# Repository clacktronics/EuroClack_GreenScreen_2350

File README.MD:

# EuroClack Green Screen 2350

EuroClack Green Screen 2350 is a **programmable Eurorack synthesizer module built around the Raspberry Pi RP2350B**. It combines stereo audio input/output, control-voltage (CV) and gate interfaces, a colour display, hands-on controls, microSD storage and USB connectivity.

The module provides a general-purpose platform for developing digital instruments, audio effects, sequencers and modulation tools within a Eurorack system. Application firmware defines its musical behaviour, while the audio, CV and gate interfaces connect it to the rest of the patch. The display and physical controls support interactive visual instruments and direct parameter editing.

The included firmware demonstrates a Tempest-inspired game and a double-pendulum simulation with sound. Effects processing, sampling and sequencing require their own application firmware.

## Main functions

| Function | Circuit | Purpose |
|---|---|---|
| Processing | U1, RP2350B in an 80-pin package | Runs the application, processes audio and CV, generates gates and manages the interface. |
| Program storage | U4, W25Q128JVS | External 128-Mbit / 16-MiB flash for firmware and stored data. |
| Additional memory provision | U15, labelled `SRAM` | Shares the QSPI data/clock bus with a separate chip select. The actual memory part and capacity are unspecified. |
| Two audio inputs | U6 TL072 stages and U5 PCM1808 | Condition analog signals and convert them to digital audio for the processor over I²S. |
| Two audio outputs | U2 PCM5102 and output filters | Convert the processor's I²S stream into left/right analog audio. |
| Four CV inputs | U13/U20 amplifier stages and MCU ADC inputs | Scale and offset external control voltages for measurement by the processor. |
| Four gate-sensing paths | U19/U21 LM393 comparators | Detect gate/trigger levels: two share CV inputs and two use dedicated gate jacks. |
| Four CV outputs | U3 MCP4728 and U8/U17 amplifier stages | Convert four digitally programmed values into analog control voltages. |
| Two gate outputs | U18/U22 SN74LVC1T45 | Translate processor logic into nominal 0/5-V gate signals through series output resistors. |
| Display and controls | SPI display connections, two push encoders and buttons | Provide graphical feedback, parameter editing and navigation. |
| Storage and expansion | microSD, external I²C, USB-C device and USB-A host connections | Provide hardware paths for files, peripherals and computer/device communication, subject to firmware support. |

There are **six physical CV/gate input jacks**: two CV-only, two shared CV/gate and two gate-only. The shared inputs are measured by both an ADC path and a comparator path, allowing firmware to read a control voltage and detect gate transitions from the same connection.

## How signals move through the circuit

```text
Audio inputs --> analog conditioning --> PCM1808 ADC --I²S--> RP2350B
Audio outputs <-- output filters <----- PCM5102 DAC <--I²S-- RP2350B

CV inputs ----> scaling and offset -----------------------> MCU ADCs
Gate inputs --> comparator thresholds -------------------> MCU GPIO
CV outputs <--- amplifier stages <----- MCP4728 DAC <------ MCU control
Gate outputs <- 3.3-V to 5-V translation <----------------- MCU GPIO

                     RP2350B
                        |
         Display / encoders / buttons / microSD / USB / I²C
```

The audio converters handle continuous sampled sound. The separate CV DAC and gate circuitry let firmware interact with other modular instruments: reading modulation, following clock or trigger events, and generating control signals. The analog stages adapt these signals to the processor and converters; their resistor ratios and reference voltages determine the actual voltage ranges.

## Display, controls and example firmware

The supplied sketches target an **NV3030B colour TFT at 280 × 240 pixels in landscape orientation**. The schematic provides parallel eight-pin header and FFC display connections; the fitted panel must match the driver and pinout.

- [Tempest demo](demo_scripts/nv3030b_tempest/nv3030b_tempest.ino): an encoder-controlled arcade-style game with audio output.
- [Double-pendulum demo](demo_scripts/nv3030b_pendulum/nv3030b_pendulum.ino): a visual physics simulation whose second pendulum's X/Y position drives the left/right audio channels.

The sketches demonstrate display rendering, encoder input and audio generation. USB MIDI, sample playback, sequencing and effects require additional application firmware. See [PERIPHERALS.md](PERIPHERALS.md) for GPIO assignments, converter configuration and firmware considerations.

## Power and physical construction

Power enters through the ten-pin Eurorack connector J18 using +12 V, ground and −12 V. The design includes MOSFET protection circuitry, switching and linear regulators for its intended 5-V and 3.3-V rails, and a 3.3-V reference with an inverted reference for CV conditioning. The analog amplifier stages use the bipolar rails. USB-C VBUS is unconnected, so this design is intended to be self-powered rather than powered from a computer's USB port.

The PCB contains processor, jack/control and SD-extension sections. A 40-way FFC links the processor and jack sections, carrying signals and power; separate connections serve the SD extension. Cable orientation and pin mapping are documented in [PERIPHERALS.md](PERIPHERALS.md).

## Current development status

This is a prototype design with documented electrical issues. The existing [DESIGN_REVIEW.md](DESIGN_REVIEW.md) reports power-supply faults, input-protection gaps, audio coupling/mute issues and incorrect CV output scaling. In particular, **the intended ±5-V CV range is not an established working capability**: the review calculates approximately 0–1.65 V for the current CV output stage. Read that review before assembly or power-up.

This README documents the module's architecture and application scope. Electrical findings and validation limits are recorded in the design review.

## Project files

- `EuroClack - Green_Screen_2350.kicad_pro` — open this project in KiCad.
- `EuroClack - Green_Screen_2350.kicad_sch` — current circuit schematic.
- `EuroClack - Green_Screen_2350.kicad_pcb` — PCB layout.
- [libraries/README.md](libraries/README.md) — bundled custom libraries and dependencies. The schematic uses KiCad 10 format; the PCB uses KiCad 9 format.
- [PERIPHERALS.md](PERIPHERALS.md) — detailed connections and firmware reference.
- [DESIGN_REVIEW.md](DESIGN_REVIEW.md) — existing engineering review and limitations.
- `demo_scripts/` — example display, controls and audio sketches.

The root PDF represents an older RP2040 design; use the native RP2350 KiCad schematic as the source for this revision.

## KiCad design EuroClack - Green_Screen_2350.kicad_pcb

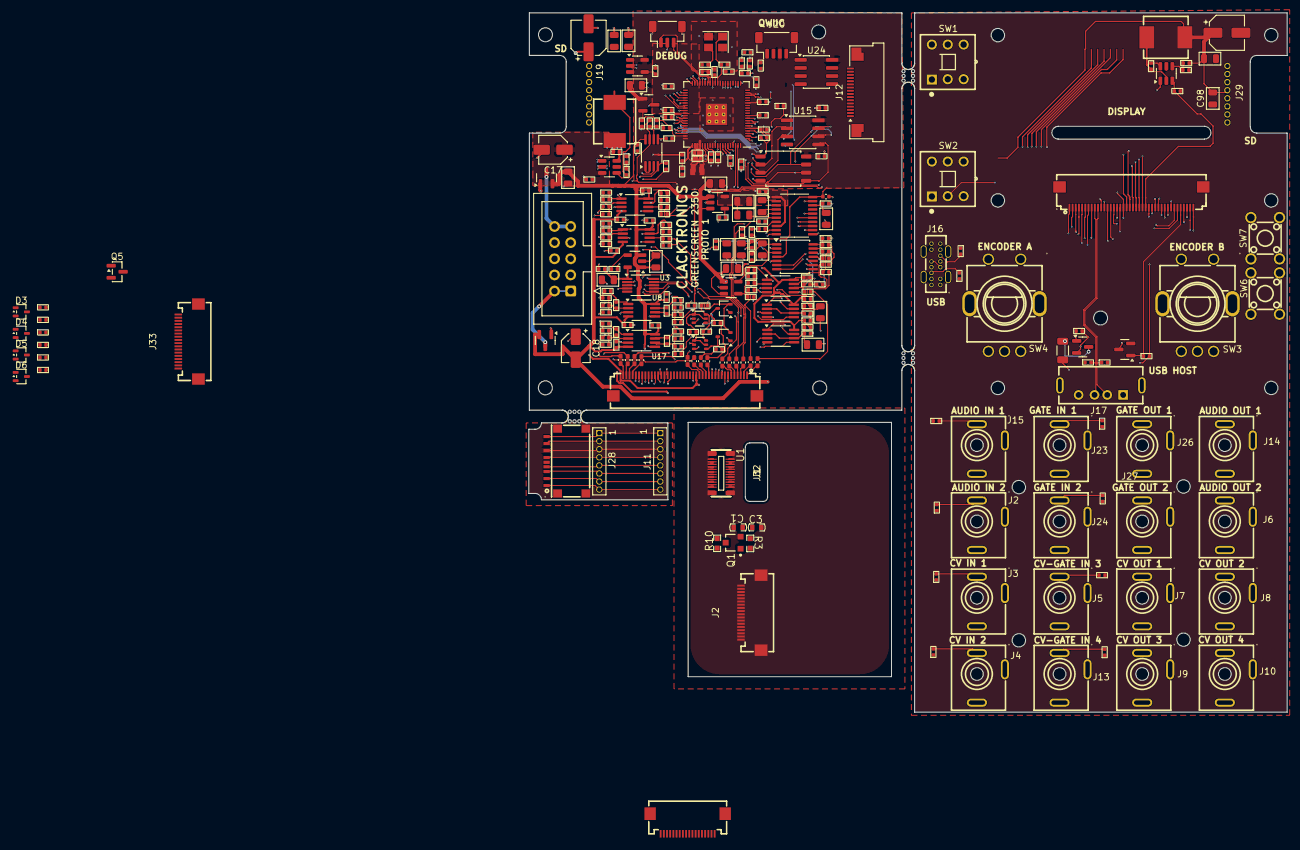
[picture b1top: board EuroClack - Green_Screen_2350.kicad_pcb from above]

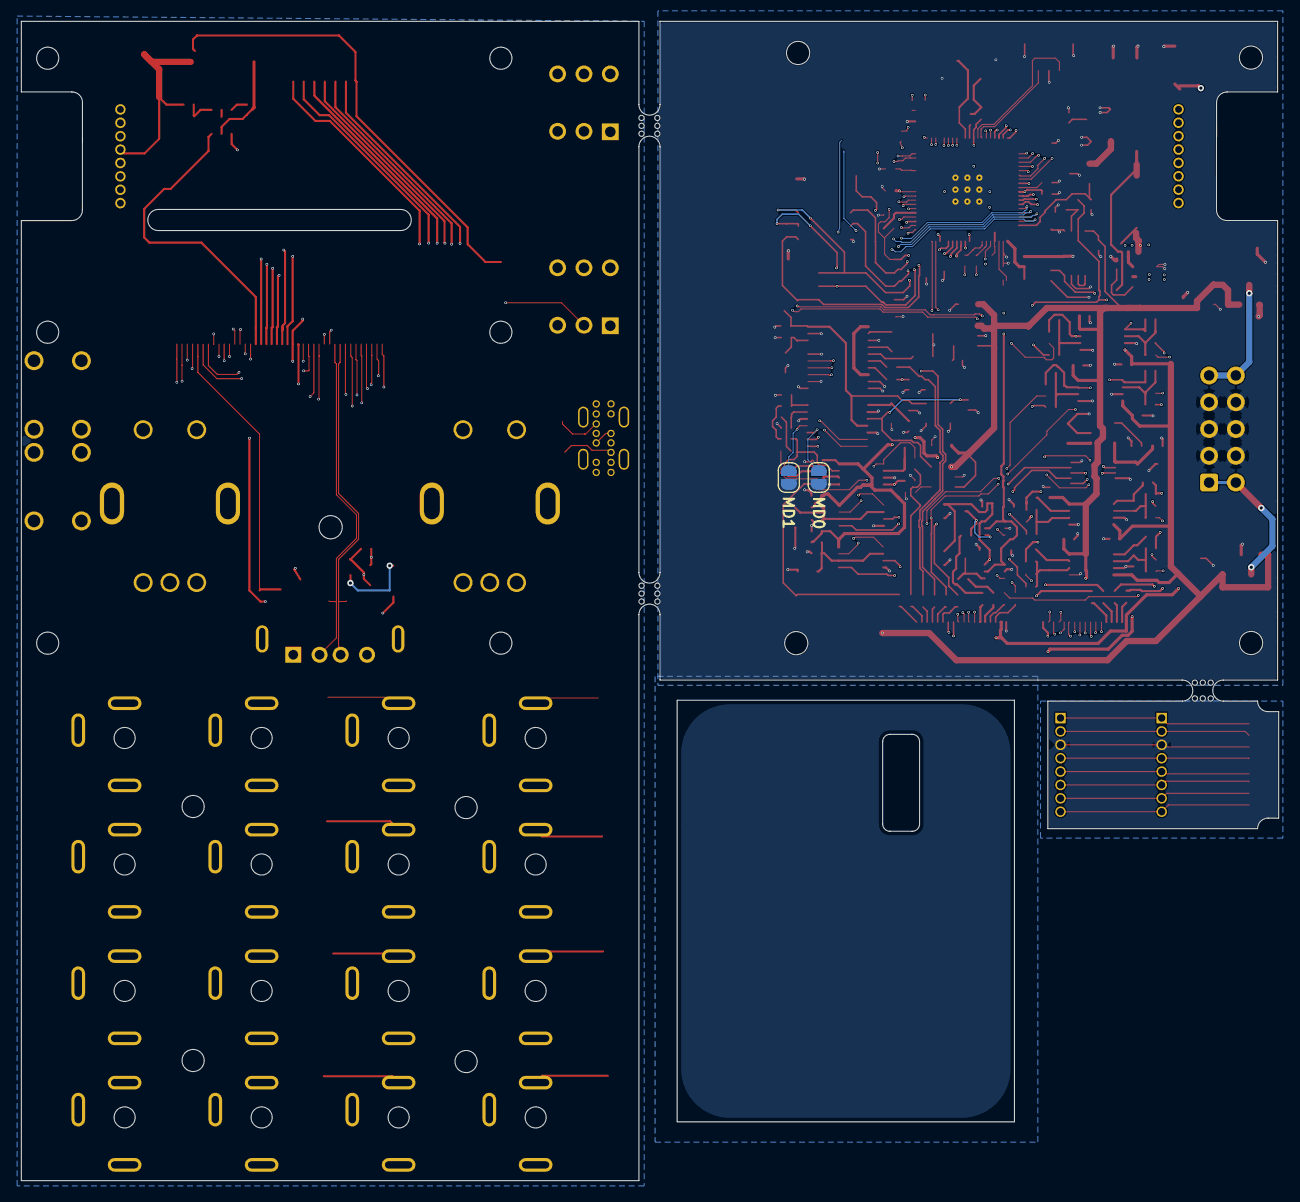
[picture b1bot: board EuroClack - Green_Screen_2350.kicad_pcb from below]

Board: 4 copper layers, 119.3 x 110.0 mm, 277 parts (2 on the bottom side), 228 nets.

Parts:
C1, C2, C7, C8: 2n2; C_0402_1005Metric
C1#2: Comment; C0603-1
C3, C6: 2u2; C_0805_2012Metric
C3#2: Comment; C0603-2
C4, C11, C13, C15, C21, C23, C24, C34, C45, C53, C57, C58, C60, C89, C95, C96, C98: 10uF; C_0805_2012Metric
C5, C12, C14, C16, C22, C25, C26, C37, C39, C40, C41, C42, C43, C44, C46, C47, C48, C49, C50, C51, C52, C54, C55, C56, C59, C61, C62, C63, C64, C70, C73, C74, C75, C76, C77, C78, C79, C80, C81, C82, C83, C84, C85, C86, C92, C93, C94, C97: 100n; C_0402_1005Metric
C9, C10: 1u; C_0402_1005Metric
C17, C18: 22uF; CP_Elec_4x5.4
C27, C28, C29, C30, C31, C32, C33, C67, C90, C91: 10p; C_0402_1005Metric
C38, C87: 220uF; CP_Elec_5x5.4
C65, C66: 15p; C_0402_1005Metric
C68, C69, C71, C72: 4.7u; C_0402_1005Metric
D1, D2, D3, D4, D5, D6: BAT54SW; SOT-323_SC-70
F1: nSMD005 150mA; R_1206_3216Metric
FB1, FB2, FB3, FB4, FB5, FB6, FB7, FB8, FB9, FB10, FB11, FB12, FB13, FB14: F; L_0402_1005Metric_Pad0.77x0.64mm_HandSolder
J1, J32: NV3030B QSPI; CONN-SMD_AXT524124
J1#2: C2982548; TF-SMD_TF-123-ARP9H15
J2, J3, J4, J5, J6, J7, J8, J9, J10, J13, J14, J15, J23, J24, J26, J27: Stereo Jack; AUDIO-TH_PJ-301C
J2#2, J3#2, J33: Conn_01x18; FPC-SMD_18P-P0.50_FPC-0.5-18P-HYH2.0
J11, J28: C22438074; CONN-TH_8P-P1.27_DEALON_DW127R-11-08-34
J12: Conn_01x16; Amphenol_F32Q-1A7x1-11016_1x16-1MP_P0.5mm_Horizontal
J16: C168704; USB-C-TH_TYPE-C-USB-14P
J17: USB_HOST; USB-A-TH_C42536
J18: Eurorack 10 pin socket; IDC-Header_2x05_P2.54mm_Vertical
J19, J29: C22438194; HDR-TH_8P-P1.27-H-M_1271WR-8P
J20: STEMMA_QT; JST_SH_BM04B-SRSS-TB_1x04-1MP_P1.00mm_Vertical
J21, J22: C2856837; FPC-SMD_40P-P0.50_XUNPU_FPC-05FB-40PH20
J25: SM03B-SRSS-TB; JST_SH_BM03B-SRSS-TB_1x03-1MP_P1.00mm_Vertical
JP1, JP2: SolderJumper_2_Open; SolderJumper-2_P1.3mm_Open_RoundedPad1.0x1.5mm
L2, L4: 10uH 4A; FXL0630-100-M
L3: 3.3u; L_pol_2016
Q1, Q4, Q5: AO3400A; SOT-23
Q1#2: Comment; SOT23A
Q2, Q3: AO3401A; SOT-23
R1, R2, R5, R15, R16, R23, R44, R53, R58, R59, R60, R61: 1k; R_0402_1005Metric
R3, R10#2: Comment; R0603
R3#2, R14, R18, R22, R25, R35, R38, R41, R50, R52, R92, R99, R100, R103, R104, R105, R106: 10k; R_0402_1005Metric
R6: 33; R_0402_1005Metric
R9, R29, R32, R46: 68k; R_0402_1005Metric
R10, R12, R27, R30, R33, R47: 33k; R_0402_1005Metric
R11, R28, R31, R34, R45, R48, R49, R51, R97, R108: 100k; R_0402_1005Metric
R13, R26, R37, R40: 6.49k; R_0402_1005Metric
R17, R36, R39, R42: 1.96k; R_0402_1005Metric
R24, R43: 27; R_0402_1005Metric
R54, R55, R56, R57: 220R; R_0402_1005Metric
R85, R86, R87, R88, R89, R90, R95, R96: 1M; R_0402_1005Metric
R91: 75k; R_0402_1005Metric
R93, R94: 5.1k; R_0402_1005Metric
R98: 22k; R_0402_1005Metric
R101, R102: R_0402_1005Metric
R107: 10R; R_0402_1005Metric
SW1, SW2: SW-TH_PS-8556DVA-6PN
SW3, SW4: RotaryEncoder_Switch; SW-TH_EC11XXXXXXXX
SW6, SW7: SW_Push; SW-TH_4P-L5.0-W5.0-P4.50-LS6.5
U1: Comment; TK014F1246-24P
U1#2: RP2350_80QFN; RP2350-QFN-80-1EP_10x10_P0.4mm_EP3.4x3.4mm_ThermalVias
U2: PCM5102; TSSOP-20_4.4x6.5mm_P0.65mm
U3: MCP4728; MSOP-10_3x3mm_P0.5mm
U4: W25Q128JVS; SOIC-8_5.3x5.3mm_P1.27mm
U5: PCM1808PWR; TSSOP-14_4.4x5mm_P0.65mm
U6, U8, U11, U13, U17, U20: TL072; MSOP-8_3x3mm_P0.65mm
U7: REF3033; SOT-23
U9, U14, U16: SPX3819M5-L-3-3; SOT-23-5
U10: SPX3819M5-L-5-0; SOT-23-5
U12, U23: TPS54302; SOT-23-6
U15: SRAM; SOIC-8_3.9x4.9mm_P1.27mm
U18, U22: SN74LVC1T45DCK; SOT-363_SC-70-6
U19, U21: LM393; MSOP-8_3x3mm_P0.65mm
U24: FM24CL16B; SOIC-8_3.9x4.9mm_P1.27mm
Y1: ABM8-272-T3; Crystal_SMD_3225-4Pin_3.2x2.5mm
mouse-bite-2mm-slot, mouse-bite-2mm-slot#2, mouse-bite-2mm-slot#3: VAL**; mouse-bite-2mm-slot

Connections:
3.3V: C1#2.1, C3#2.1, R3.1, U1.15, U1.17, U1.23
$1N2: Q1#2.3, R10#2.1
+1V1: C69.1, C70.1, C72.1, C73.1, L3.1, U1#2.10 (DVDD), U1#2.32 (DVDD), U1#2.51 (DVDD), U1#2.65 (VREG_FB)
+3.3V: C15.1, C16.1, C55.1, C63.1, C64.1, C68.1, C74.1, C75.1, C76.1, C77.1, C78.1, C79.1, C80.1, C81.2, C82.1, C83.1, C93.2, J1.15, J1.17, J1.23, J2#2.3, J2#2.4, J2#2.17, J3#2.1, J20.3, J32.15, J32.17, J32.23, J33.3, J33.4, J33.17, R3#2.1, R6.1, R22.1, R103.2, R104.2, R105.2, R106.2, U1#2.5 (IOVDD), U1#2.15 (IOVDD), U1#2.24 (IOVDD), U1#2.29 (IOVDD), U1#2.41 (IOVDD), U1#2.50 (IOVDD), U1#2.60 (IOVDD), U1#2.64 (VREG_VIN), U1#2.68 (USB_OTP_VDD), U1#2.69 (QSPI_IOVDD), U1#2.76 (IOVDD), U2.17 (XSMT), U2.20 (DVDD), U4.8 (VCC), U5.4 (VDD), U14.5 (OUT), U15.8 (VCC), U18.1 (VCCA), U18.5 (DIR), U22.1 (VCCA), U22.5 (DIR), U24.8 (VDD)
+3.3VA: C21.1, C22.1, U3.1 (VDD), U9.5 (OUT)
+5V: C38.1, C57.1, C58.1, C60.1, C92.1, C94.1, D1.2 (K), D2.2 (K), D3.2 (K), D4.2 (K), D5.2 (K), D6.2 (K), J21.17, L2.2, R91.2, U7.1 (IN), U14.1 (IN), U14.3 (EN), U18.6 (VCCB), U22.6 (VCCB)
+5VA: C13.1, C14.1, U5.3 (VCC), U10.5 (OUT)
+12V: C17.1, C23.1, C24.1, C39.1, C41.1, C43.1, C46.1, C47.1, C49.1, C51.1, C59.2, C62.1, C85.2, C95.2, C96.1, J21.25, Q2.2 (S), R49.2, R51.2, U6.8 (V+), U8.8 (V+), U9.1 (IN), U9.3 (EN), U10.1 (IN), U10.3 (EN), U11.8 (V+), U12.3 (VIN), U13.8 (V+), U16.1 (IN), U16.3 (EN), U17.8 (V+), U19.8 (V+), U20.8 (V+), U21.8 (V+), U23.3 (VIN)
-12V: C18.2, C40.1, C42.1, C44.1, C48.1, C50.1, C52.1, Q1.2 (S), U6.4 (V-), U8.4 (V-), U11.4 (V-), U13.4 (V-), U17.4 (V-), U20.4 (V-)
/3V3_DAC: C53.1, C54.1, U2.1 (CPVDD), U2.8 (AVDD), U16.5 (OUT)
/3V3_SD_SCREEN: C87.1, C89.1, C98.1, J12.8, J12.9, J12.16, J29.5, L4.2, R97.2
/5V_JACK: J22.17, Q3.2 (S), R99.2, R100.2
/AUDIO_IN_1_JACK: J15.T, J22.1, R86.2
/AUDIO_IN_1_MICRO: FB1.1, J21.1
/AUDIO_IN_2_JACK: J2.T, J22.2, R85.2
/AUDIO_IN_2_MICRO: FB2.1, J21.2
/AUDIO_L_IN: C10.1, C27.2, R12.2, U6.7
/AUDIO_OUT_1_JACK: J14.T, J22.3
/AUDIO_OUT_1_MICRO: FB6.2, J21.3
/AUDIO_OUT_2_JACK: J6.T, J22.4
/AUDIO_OUT_2_MICRO: FB7.2, J21.4
/AUDIO_R_IN: C9.1, C28.2, R27.2, U6.1
/CV_GATE_IN_3_JACK: J5.T, J22.5, R89.2
/CV_GATE_IN_3_MICRO: FB12.1, J21.5
/CV_GATE_IN_4_JACK: J13.T, J22.6, R90.2
/CV_GATE_IN_4_MICRO: FB5.1, J21.6
/CV_IN_1: FB3.2, R31.1
/CV_IN_1_JACK: J3.T, J22.15, R87.2
/CV_IN_1_MICRO: FB3.1, J21.15
/CV_IN_2_JACK: J4.T, J22.16, R88.2
/CV_IN_2_MICRO: FB4.1, J21.16
/CV_OUT_1: FB8.1, R18.2, R57.2
/CV_OUT_1_JACK: J7.T, J22.40
/CV_OUT_1_MICRO: FB8.2, J21.40
/CV_OUT_2: FB9.1, R35.2, R56.2
/CV_OUT_2_JACK: J8.T, J22.37
/CV_OUT_2_MICRO: FB9.2, J21.37
/CV_OUT_3: FB10.1, R38.2, R55.2
/CV_OUT_3_JACK: J9.T, J22.39
/CV_OUT_3_MICRO: FB10.2, J21.39
/CV_OUT_4: FB11.1, R41.2, R54.2
/CV_OUT_4_JACK: J10.T, J22.38
/CV_OUT_4_MICRO: FB11.2, J21.38
/ENC1_A_JACK: J22.31, SW3.A
/ENC1_A_MICRO: J21.31, U1#2.37 (GPIO29)
/ENC1_B_JACK: J22.32, SW3.B
/ENC1_B_MICRO: J21.32, U1#2.38 (GPIO30)
/ENC1_SW_JACK: J22.30, SW3.S1
/ENC1_SW_MICRO: J21.30, U1#2.36 (GPIO28)
/ENC2_A_JACK: J22.34, SW4.A
/ENC2_A_MICRO: J21.34, U1#2.40 (GPIO32)
/ENC2_B_JACK: J22.35, SW4.B
/ENC2_B_MICRO: J21.35, U1#2.42 (GPIO33)
/ENC2_SW_JACK: J22.33, SW4.S1
/ENC2_SW_MICRO: J21.33, U1#2.39 (GPIO31)
/GATE_IN_1_JACK: J22.7, J23.T, R95.2
/GATE_IN_1_MICRO: J21.7, R61.1
/GATE_IN_2_JACK: J22.8, J24.T, R96.2
/GATE_IN_2_MICRO: J21.8, R60.1
/GATE_OUT_1_JACK: J22.13, J26.T
/GATE_OUT_1_MICRO: FB14.2, J21.13
/GATE_OUT_2_JACK: J22.14, J27.T
/GATE_OUT_2_MICRO: FB13.2, J21.14
/GND_JACK: C98.2, J2.S, J3.S, J4.S, J5.S, J6.S, J7.S, J8.S, J9.S, J10.S, J13.S, J14.S, J15.S, J16.A1 (GND), J16.A12 (GND), J16.B1 (GND), J16.B12 (GND), J16.S1 (SHIELD), J17.4 (GND), J17.5 (Shield), J22.18, J23.S, J24.S, J26.S, J27.S, J29.3, Q4.2 (S), R85.1, R86.1, R87.1, R88.1, R89.1, R90.1, R93.1, R94.1, R95.1, R96.1, R101.1, R102.2, SW1.1, SW2.1, SW3.C, SW3.S2, SW4.C, SW4.S2, SW6.1, SW7.1
/HSTX12_DC: J12.1, U1#2.11 (GPIO12)
/HSTX13_CS: J12.2, U1#2.12 (GPIO13)
/HSTX14_SCK: J12.3, U1#2.13 (GPIO14)
/HSTX15_DIN: J12.4, U1#2.14 (GPIO15)
/HSTX16_RST: J12.5, U1#2.16 (GPIO16)
/HSTX17_BLK: R107.2, R108.1, U1#2.17 (GPIO17)
/I2C_DAC_SCL: J21.21, R105.1, U1#2.22 (GPIO22), U3.2 (SCL)
/I2C_DAC_SDA: J21.22, R106.1, U1#2.23 (GPIO23), U3.3 (SDA)
/I2S_ADC_BCK: U1#2.7 (GPIO9), U5.8 (BCK)
/I2S_ADC_DOUT: U1#2.9 (GPIO11), U5.9 (DOUT)
/I2S_ADC_LRCK: U1#2.8 (GPIO10), U5.7 (LRCK)
/I2S_ADC_MD0: JP2.2 (B), U5.10 (MD0)
/I2S_ADC_MD1: JP1.2 (B), U5.11 (MD1)
/I2S_ADC_SCKI: U1#2.21 (GPIO21), U5.6 (SCKI)
/I2S_DAC_BCK: U1#2.3 (GPIO6), U2.13 (BCK)
/I2S_DAC_DIN: U1#2.6 (GPIO8), U2.14 (DIN)
/I2S_DAC_LRCK: U1#2.4 (GPIO7), U2.15 (LRCK)
/LCD_CS: J1.1, J2#2.8, J3#2.7, J32.1, J33.8
/LCD_DC: J2#2.7, J3#2.8, J33.7
/LCD_RST: J1.9, J2#2.11, J32.9, J33.11
/LCD_TE: J1.14, J3#2.11, J32.14
/LEDK: J1.16, J2#2.2, J32.16, J33.2
/LED_K: J12.6, Q5.3 (D)
/MCU_CV_IN_1: C29.2, R30.2, U1#2.49 (GPIO40_ADC0), U13.1
/MCU_CV_IN_2: C30.2, R33.2, U1#2.52 (GPIO41_ADC1), U13.7
/MCU_CV_IN_3: C32.2, R10.2, U1#2.53 (GPIO42_ADC2), U20.1
/MCU_CV_IN_4: C33.2, R47.2, U1#2.54 (GPIO43_ADC3), U20.7
/MCU_GATE_IN_1: U1#2.55 (GPIO44_ADC4), U21.1
/MCU_GATE_IN_2: U1#2.56 (GPIO45_ADC5), U21.7
/MCU_GATE_IN_3: U1#2.57 (GPIO46_ADC6), U19.1
/MCU_GATE_IN_4: U1#2.58 (GPIO47_ADC7), U19.7
/MCU_GATE_OUT_1: U1#2.18 (GPIO18), U18.3 (A)
/MCU_GATE_OUT_2: U1#2.19 (GPIO19), U22.3 (A)
/QSPI_D1: J1.3, J3#2.4, J32.3
/QSPI_D2: J1.6, J3#2.5, J32.6
/QSPI_D3: J1.5, J3#2.6, J32.5
/QSPI_SCLK: U1#2.71 (QSPI_SCLK), U4.6 (CLK), U15.6 (CLK)
/QSPI_SD0: U1#2.72 (QSPI_SD0), U4.5 (DI(IO0)), U15.5 (DI(IO0))
/QSPI_SD1: U1#2.74 (QSPI_SD1), U4.2 (DO(IO1)), U15.2 (DO(IO1))
/QSPI_SD2: U1#2.73 (QSPI_SD2), U4.3 (IO2), U15.3 (IO2)
/QSPI_SD3: U1#2.70 (QSPI_SD3), U4.7 (IO3), U15.7 (IO3)
/SD_CLK: J19.5, U1#2.43 (GPIO34)
/SD_CMD: J19.3, U1#2.44 (GPIO35)
/SD_DAT0: J19.7, U1#2.45 (GPIO36)
/SD_DAT1: J19.8, U1#2.46 (GPIO37)
/SD_DAT2: J19.1, U1#2.47 (GPIO38)
/SD_DAT3: J19.2, U1#2.48 (GPIO39)
/SD_GND: J1#2.6 (VSS), J11.3, J28.3
/SPI MOSI: J1.2, J2#2.10, J3#2.3, J32.2, J33.10
/SPI_SCK: J1.4, J2#2.9, J3#2.2, J32.4, J33.9
/STEMMA_SCL: J12.12, J20.1, J21.19, R103.1, U1#2.2 (GPIO5), U24.6 (SCL)
/STEMMA_SDA: J12.13, J20.2, J21.20, R104.1, U1#2.1 (GPIO4), U24.5 (SDA)
/SWCLK: J25.1, U1#2.33 (SWCLK)
/SWD: J25.3, U1#2.34 (SWD)
/SW_RUN_JACK: J22.27, SW7.2
/SW_USR1_JACK: J22.28, SW1.2
/SW_USR2_JACK: J22.29, SW2.2
/TP_INT: J1.22, J2#2.16, J3#2.14, J12.15, J32.22, J33.16
/TP_RST: J1.21, J2#2.15, J12.14, J32.21, J33.15
/TP_SCL: J1.19, J2#2.13, J3#2.12, J32.19, J33.13
/TP_SDA: J1.20, J2#2.14, J3#2.13, J32.20, J33.14
/USB_DM_JACK: J16.A7 (D-), J16.B7 (D-), J22.12
/USB_DN: J21.12, R43.1
/USB_DP: J21.11, R24.1
/USB_DP_JACK: J16.A6 (D+), J16.B6 (D+), J22.11
/USB_HOST_DM_JACK: J17.2 (D-), J22.10, R102.1
/USB_HOST_DM_MICRO: J21.10, U1#2.78 (GPIO1)
/USB_HOST_DP_JACK: J17.3 (D+), J22.9, R101.2
/USB_HOST_DP_MICRO: J21.9, U1#2.79 (GPIO2)
/VREF_ADC: C37.1, C84.1, R25.1, U1#2.59 (ADC_AVDD), U7.2 (OUT)
/VREF_ADC_NEG: R9.1, R13.1, R14.2, R26.1, R29.1, R32.1, R37.1, R40.1, R46.1, U11.7
/VREG_AVDD: C71.1, R6.2, U1#2.61 (VREG_AVDD)
/VREG_LX: L3.2, U1#2.63 (VREG_LX)
/XIN: C65.1, U1#2.30 (XIN), Y1.1
/XOUT: R5.1, U1#2.31 (XOUT)
/~PSRAM_CS: R22.2, U1#2.77 (GPIO0), U15.1 (~CS)
/~QSPI_SS: R3#2.2, R23.1, U1#2.75 (QSPI_SS), U4.1 (~CS)
/~SW_MENU_BOOT_JACK: J22.26, SW6.2
/~SW_MENU_BOOT_MICRO: J21.26, R23.2, U1#2.26 (GPIO25)
/~SW_RUN_MICRO: J21.27, U1#2.35 (RUN)
/~SW_USR1_MICRO: J21.28, U1#2.27 (GPIO26)
/~SW_USR2_MICRO: J21.29, U1#2.28 (GPIO27)
/~USBH_PWR_EN_JACK: J22.36, Q4.1 (G), R100.1
/~USBH_PWR_EN_MICRO: J21.36, U1#2.25 (GPIO24)
BL_CTR: Q1#2.1, R3.2
GND: C1.2, C1#2.2, C2.2, C3#2.2, C4.2, C5.2, C6.2, C7.2, C8.2, C11.2, C12.2, C13.2, C14.2, C15.2, C16.2, C17.2, C18.1, C21.2, C22.2, C23.2, C24.2, C25.2, C26.2, C34.2, C37.2, C38.2, C39.2, C40.2, C41.2, C42.2, C43.2, C44.2, C45.2, C46.2, C47.2, C48.2, C49.2, C50.2, C51.2, C52.2, C53.2, C54.2, C55.2, C57.2, C58.2, C59.1, C60.2, C61.2, C62.2, C63.2, C64.2, C65.2, C66.2, C68.2, C69.2, C70.2, C71.2, C72.2, C73.2, C74.2, C75.2, C76.2, C77.2, C78.2, C79.2, C80.2, C81.1, C82.2, C83.2, C84.2, C85.1, C87.2, C89.2, C92.2, C93.1, C94.2, C95.1, C96.2, C97.2, D1.1 (A), D2.1 (A), D3.1 (A), D4.1 (A), D5.1 (A), D6.1 (A), J1.13, J1.18, J1.24, J2#2.1, J2#2.5, J2#2.6, J2#2.12, J2#2.18, J3#2.15, J12.10, J12.11, J18.3, J18.4, J18.5, J18.6, J18.7, J18.8, J20.4, J21.18, J25.2, J25.MP (MountPin), J32.13, J32.18, J32.24, J33.1, J33.5, J33.6, J33.12, J33.18, JP1.1 (A), JP2.1 (A), Q1.1 (G), Q1#2.2, Q2.1 (G), Q5.2 (S), R50.1, R52.1, R92.1, R98.1, R108.2, U1.13, U1.18, U1.24, U1.25, U1#2.62 (VREG_PGND), U1#2.81 (GND), U2.3 (CPGND), U2.9 (AGND), U2.10 (DEMP), U2.11 (FLT), U2.12 (SCK), U2.16 (FMT), U2.19 (DGND), U3.4 (~LDAC), U3.10 (VSS), U4.4 (GND), U5.2 (AGND), U5.5 (DGND), U5.12 (FMT), U6.3 (+), U6.5 (+), U7.3 (GND), U8.3 (+), U8.5 (+), U9.2 (GND), U10.2 (GND), U11.3 (+), U11.5 (+), U12.1 (GND), U13.3 (+), U13.5 (+), U14.2 (GND), U15.4 (GND), U16.2 (GND), U17.3 (+), U17.5 (+), U18.2 (GND), U19.4 (V-), U20.3 (+), U20.5 (+), U21.4 (V-), U22.2 (GND), U23.1 (GND), U24.4 (VSS), Y1.2, Y1.4
LED-: R10#2.2, U1.16
unnamed: C1.1, FB6.1, R1.2
unnamed: C2.1, FB7.1, R2.2
unnamed: C9.2, R16.1
unnamed: C10.2, R15.1
unnamed: C31.2, R57.1, U8.1
unnamed: C66.1, R5.2, Y1.3
unnamed: C67.2, R56.1, U8.7
unnamed: C90.2, R55.1, U17.1
unnamed: C91.2, R54.1, U17.7
unnamed: D1.3 (COM), R53.1, U22.4 (B)
unnamed: D2.3 (COM), R44.1, U18.4 (B)
unnamed: D3.3 (COM), R60.2, U21.5 (+)
unnamed: D4.3 (COM), R61.2, U21.3 (+)
unnamed: D5.3 (COM), R59.2, U19.5 (+)
unnamed: D6.3 (COM), R58.2, U19.3 (+)
unnamed: FB1.2, R11.1
unnamed: FB2.2, R28.1
unnamed: FB4.2, R34.1
unnamed: FB5.2, R48.1, R59.1
unnamed: FB12.2, R45.1, R58.1
unnamed: FB13.1, R53.2
unnamed: FB14.1, R44.2
unnamed: J1#2.5 (CLK), J11.4, J28.4
unnamed: J1#2.3 (CMD), J11.6, J28.6
unnamed: J1#2.7 (DAT0), J11.2, J28.2
unnamed: J1#2.8 (DAT1), J11.1, J28.1
unnamed: J1#2.1 (DAT2), J11.8, J28.8
unnamed: J1#2.2 (DAT3/CD), J11.7, J28.7
unnamed: J1#2.4 (VDD), J11.5, J28.5
unnamed: J16.A5 (CC1), R93.2
unnamed: J16.B5 (CC2), R94.2
unnamed: F1.2, J17.1 (VBUS)
unnamed: J18.1, J18.2, Q1.3 (D)
unnamed: J18.9, J18.10, Q2.3 (D)
unnamed: F1.1, Q3.3 (D)
unnamed: Q3.1 (G), Q4.3 (D), R99.1
unnamed: Q5.1 (G), R107.1
unnamed: R43.2, U1#2.66 (USB_DM)
unnamed: R24.2, U1#2.67 (USB_DP)
unnamed: C3.2, U2.4 (CAPM)
unnamed: C3.1, U2.2 (CAPP)
unnamed: C4.1, C5.1, U2.18 (LDOO)
unnamed: R1.1, U2.6 (OUTL)
unnamed: R2.1, U2.7 (OUTR)
unnamed: C6.1, U2.5 (VNEG)
unnamed: R17.1, U3.6 (VOUTA)
unnamed: R36.1, U3.7 (VOUTB)
unnamed: R39.1, U3.8 (VOUTC)
unnamed: R42.1, U3.9 (VOUTD)
unnamed: C7.1, R16.2, U5.13 (VINL)
unnamed: C8.1, R15.2, U5.14 (VINR)
unnamed: C11.1, C12.1, U5.1 (VREF)
unnamed: C28.1, R27.1, R28.2, U6.2 (-)
unnamed: C27.1, R11.2, R12.1, U6.6 (-)
unnamed: C31.1, R13.2, R17.2, R18.1, U8.2 (-)
unnamed: C67.1, R26.2, R35.1, R36.2, U8.6 (-)
unnamed: C25.1, U9.4 (BP)
unnamed: C26.1, U10.4 (BP)
unnamed: U11.1, U11.2 (-)
unnamed: R14.1, R25.2, U11.6 (-)
unnamed: C56.1, U12.6 (BOOT)
unnamed: R91.1, R92.2, U12.4 (FB)
unnamed: C56.2, L2.1, U12.2 (SW)
unnamed: C29.1, R29.2, R30.1, R31.2, U13.2 (-)
unnamed: C30.1, R32.2, R33.1, R34.2, U13.6 (-)
unnamed: C61.1, U14.4 (BP)
unnamed: C97.1, U16.4 (BP)
unnamed: C90.1, R37.2, R38.1, R39.2, U17.2 (-)
unnamed: C91.1, R40.2, R41.1, R42.2, U17.6 (-)
unnamed: C34.1, R49.1, R50.2, U19.2 (-), U19.6 (-)
unnamed: C32.1, R9.2, R10.1, R45.2, U20.2 (-)
unnamed: C33.1, R46.2, R47.1, R48.2, U20.6 (-)
unnamed: C45.1, R51.1, R52.2, U21.2 (-), U21.6 (-)
unnamed: C86.1, U23.6 (BOOT)
unnamed: R97.1, R98.2, U23.4 (FB)
unnamed: C86.2, L4.1, U23.2 (SW)
RST: U1.9, U1.21

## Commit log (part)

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2025-04-22 First dump of files
2025-04-22 work on connectors layout
2026-01-05 Added ground pour to panel and asjusted nets to suit
2026-01-06 little bits
2026-01-06 Tweaks
2026-01-19 Updated pinouts to work better
2026-01-23 CHAGNES
2026-02-16 misc changes
2026-02-24 Panel routing
2026-03-03 Physical prototypes tested, needed shifting
2026-03-06 More changes
2026-04-16 Prototype pushed
2026-05-11 Beginning of demos
2026-05-11 Errors list
